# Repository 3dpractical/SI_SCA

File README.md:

# SI_SCA - Documentation

Si-SCA is a project to monitor heart rate and gyro status using Bluetooth Low Energy devices based on ESP32. This repository contain firmware for the devices to be installed.

## Library Used

 - [Adafruit MPU 6050](https://github.com/adafruit/Adafruit_MPU6050)
 - [NimBLE](https://github.com/h2zero/esp-nimble-cpp)
 - [RGB LED](https://github.com/FastLED/FastLED)
 - [FreeRTOS](https://docs.espressif.com/projects/esp-idf/en/latest/esp32/api-reference/system/freertos.html)
 - [TaskScheduler](https://github.com/arkhipenko/TaskScheduler)

## To-Do-List

- [X] ~~Establish Bluetooth Connection~~
- [X] ~~AD8232 HR Sensor Research~~
- [X] ~~Validate and Calibrate HR data~~
- [X] ~~MPU6050 get fixed Gyro data~~
- [X] ~~Validate and Calibrate Gyro data~~
- [X] ~~Get Battery Percentage Level~~
- [X] ~~Update BLE using NimBLE~~
- [X] ~~Add RGB Indicator~~
- [X] ~~Add Buzzer Indicator~~
- [X] ~~Configure Sleep Mode~~
- [X] ~~Import RTOS for better timing management~~
- [ ] Add AI for ECG signal detector

## License
This project is licensed under the MIT License - see the [LICENSE.md](LICENSE) file for details.

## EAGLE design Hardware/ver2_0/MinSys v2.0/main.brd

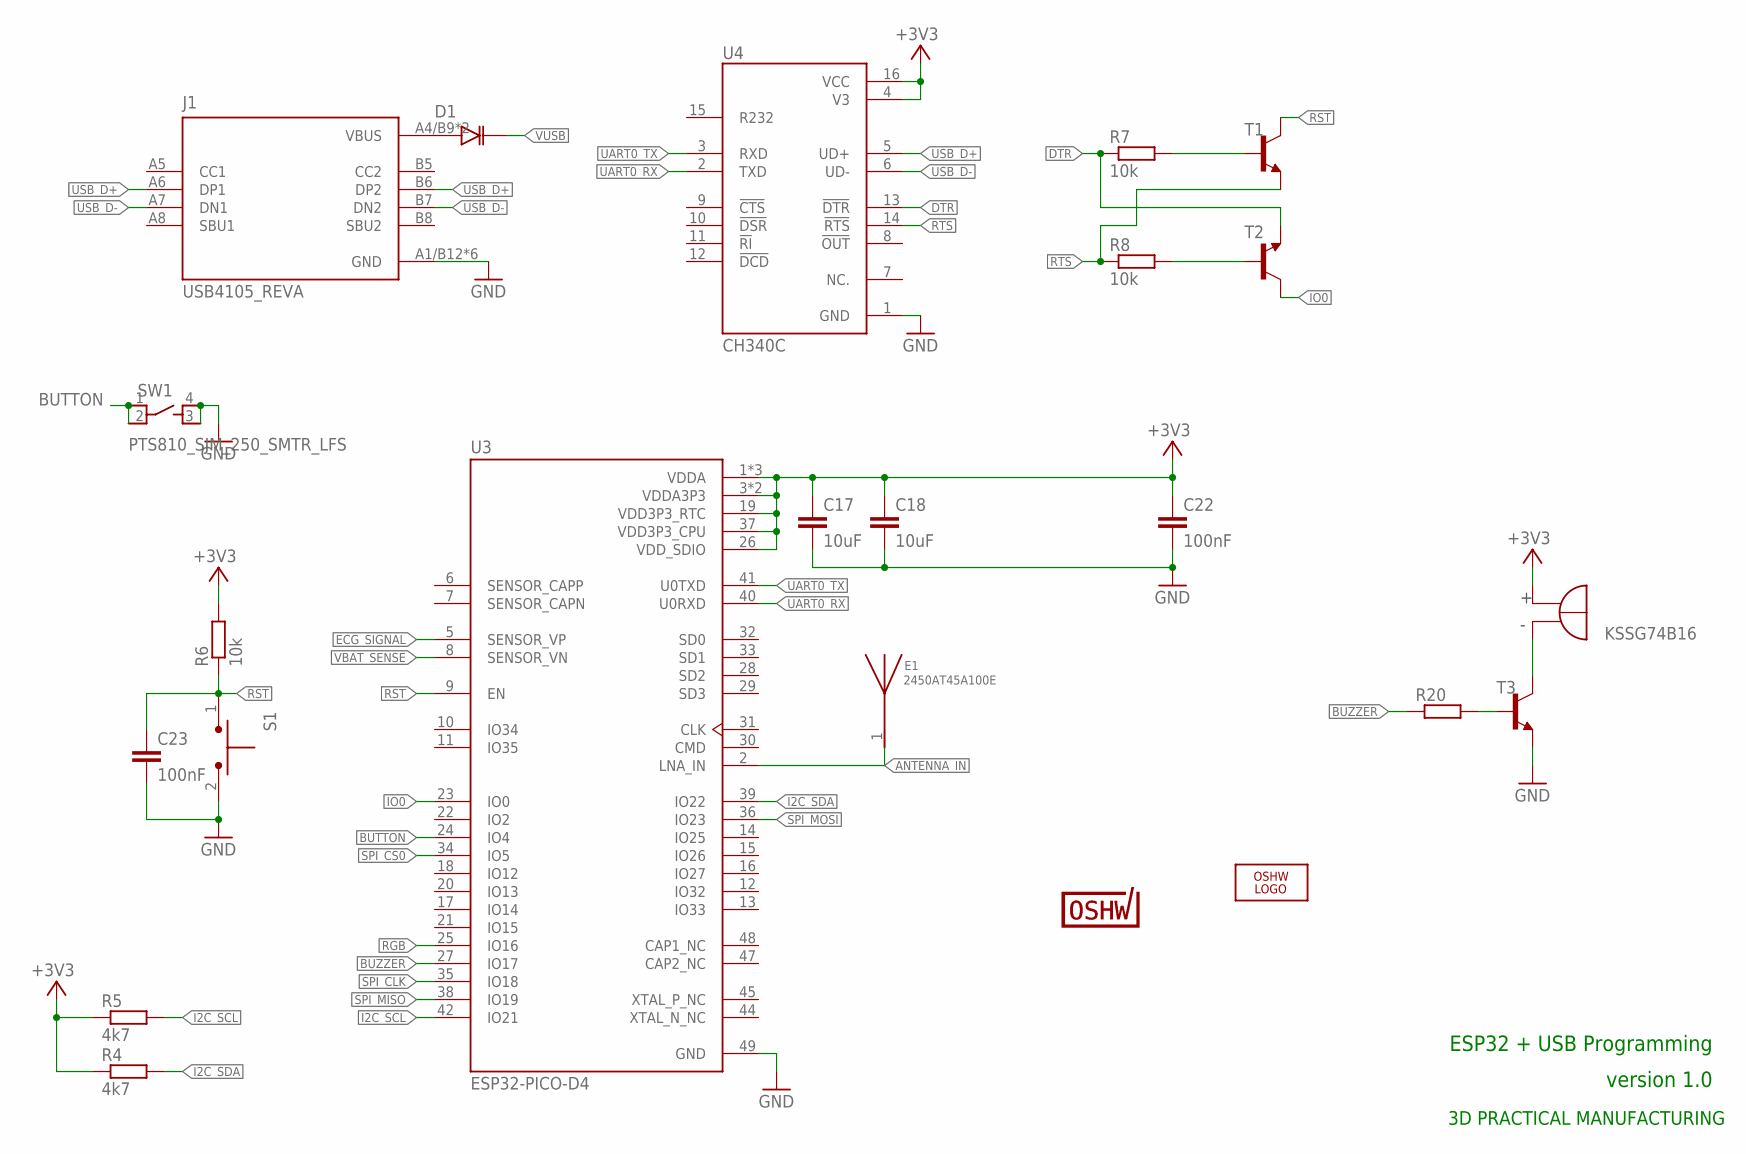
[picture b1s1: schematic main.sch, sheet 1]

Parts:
C17, C18: 10uF; C0603
C22, C23: 100nF; C0603
D1: ZMV829BTA; SOD2512X116N
E1: 2450AT45A100E; ANT_2450AT45A100E
J1: USB4105_REVA; GCT_USB4105_REVA
LOGO2: OSHW_LOGO_FILLX0200-NT; OSHW_FILLX200_NOTEXT
LS1: KSSG74B16; XDCR_KSSG74B16
R4, R5: 4k7; R0603
R6, R7, R8: 10k; R0603
R20: R-EU_R0603; R0603
S1: TL1015AF160QG; SW_TL1015AF160QG
SW1: PTS810_SJM_250_SMTR_LFS; SW_PTS810_SJM_250_SMTR_LFS
T1, T2, T3: MMBT4401LT1-NPN-SOT23-BEC; SOT23-BEC
U3: ESP32-PICO-D4; PQFN50P700X700X104-49N
U4: CH340C; SOIC127P600X180-16N
U$10: CERT-SMALL; CERT-SMALL-SILK

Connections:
+3V3: C17.1, C18.1, C22.1, LS1.P (POS), R4.1, R5.1, R6.2, U3.1 (VDDA), U3.3 (VDDA3P3), U3.4 (VDDA3P3), U3.19 (VDD3P3_RTC), U3.26 (VDD_SDIO), U3.37 (VDD3P3_CPU), U3.43 (VDDA), U3.46 (VDDA), U4.4 (V3), U4.16 (VCC); also elsewhere on the board
ANTENNA_IN: E1.1, U3.2 (LNA_IN)
BUTTON: SW1.1, SW1.2, U3.24 (IO4)
BUZZER: R20.1, U3.27 (IO17)
DTR: R7.1, T2.E, U4.13 (!DTR)
ECG_SIGNAL: U3.5 (SENSOR_VP); also elsewhere on the board
GND: C17.2, C18.2, C22.2, C23.2, J1.A1/B12 (GND), J1.B1/A12 (GND), J1.G1 (GND), J1.G2 (GND), J1.G3 (GND), J1.G4 (GND), S1.2, SW1.3, SW1.4, T3.E, U3.49 (GND), U4.1 (GND); also elsewhere on the board
I2C_SCL: R5.2, U3.42 (IO21); also elsewhere on the board
I2C_SDA: R4.2, U3.39 (IO22); also elsewhere on the board
IO0: T2.C, U3.23 (IO0)
unnamed: R7.2, T1.B
unnamed: R8.2, T2.B
unnamed: R20.2, T3.B
unnamed: D1.A, J1.A4/B9 (VBUS), J1.B4/A9 (VBUS)
unnamed: LS1.N (NEG), T3.C
RGB: U3.25 (IO16); also elsewhere on the board
RST: C23.1, R6.1, S1.1, T1.C, U3.9 (EN)
RTS: R8.1, T1.E, U4.14 (!RTS)
SPI_CLK: U3.35 (IO18)
SPI_CS0: U3.34 (IO5)
SPI_MISO: U3.38 (IO19)
SPI_MOSI: U3.36 (IO23)
UART0_RX: U3.40 (U0RXD), U4.2 (TXD)
UART0_TX: U3.41 (U0TXD), U4.3 (RXD)
USB_D+: J1.A6 (DP1), J1.B6 (DP2), U4.5 (UD+)
USB_D-: J1.A7 (DN1), J1.B7 (DN2), U4.6 (UD-)
VBAT_SENSE: U3.8 (SENSOR_VN); also elsewhere on the board
VUSB: D1.K; also elsewhere on the board

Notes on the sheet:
ESP32 + USB Programming
3D PRACTICAL MANUFACTURING
version 1.0

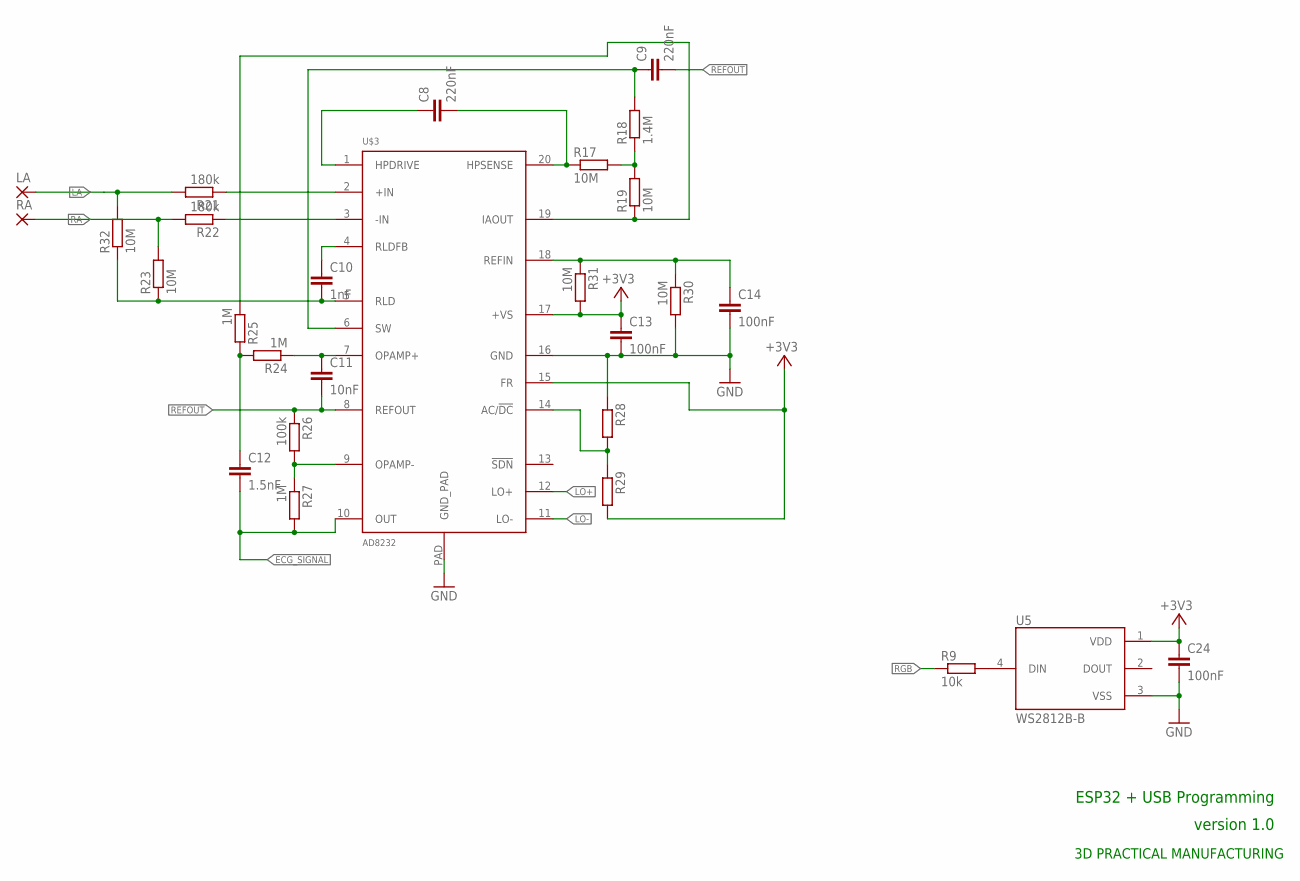
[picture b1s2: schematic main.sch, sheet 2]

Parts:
C8, C9: 220nF; C0603
C10: 1nF; C0603
C11: 10nF; C0603
C12: 1.5nF; C0603
C13, C14, C24: 100nF; C0603
LA: SMD2; SMD1,27-2,54
R9: 10k; R0603
R17, R19, R23, R30, R31, R32: 10M; R0603
R18: 1.4M; R0603
R21, R22: 180k; R0603
R24, R25, R27: 1M; R0603
R26: 100k; R0603
R28, R29: R-EU_R0603; R0603
RA: SMD2; SMD1,27-2,54
U5: WS2812B-B; LED_WS2812B-B
U$3: AD8232; LFCSP_20

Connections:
+3V3: C13.1, C24.1, R29.2, R31.2, U5.1 (VDD), U$3.15 (FR), U$3.17 (+VS); also elsewhere on the board
ECG_SIGNAL: C12.2, R27.2, U$3.10 (OUT); also elsewhere on the board
GND: C13.2, C14.2, C24.2, R28.1, R30.2, U5.3 (VSS), U$3.16 (GND), U$3.PAD (GND_PAD); also elsewhere on the board
LA: LA.1, R21.2, R32.2
LO+: U$3.12 (LO+)
LO-: U$3.11 (LO-)
unnamed: R9.2, U5.4 (DIN)
unnamed: C8.2, R17.1, U$3.20 (HPSENSE)
unnamed: C8.1, U$3.1 (HPDRIVE)
unnamed: R19.1, R25.1, U$3.19 (IAOUT)
unnamed: R17.2, R18.1, R19.2
unnamed: C9.1, R18.2, U$3.6 (SW)
unnamed: C12.1, R24.2, R25.2
unnamed: R21.1, U$3.2 (+IN)
unnamed: R22.1, U$3.3 (-IN)
unnamed: C10.1, U$3.4 (RLDFB)
unnamed: C10.2, R23.1, R32.1, U$3.5 (RLD)
unnamed: C11.1, R24.1, U$3.7 (OPAMP+)
unnamed: R26.2, R27.1, U$3.9 (OPAMP-)
unnamed: R28.2, R29.1, U$3.14 (AC/!DC)
unnamed: C14.1, R30.1, R31.1, U$3.18 (REFIN)
RA: R22.2, R23.2, RA.1
REFOUT: C9.2, C11.2, R26.1, U$3.8 (REFOUT)
RGB: R9.1; also elsewhere on the board

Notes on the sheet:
ESP32 + USB Programming
3D PRACTICAL MANUFACTURING
version 1.0

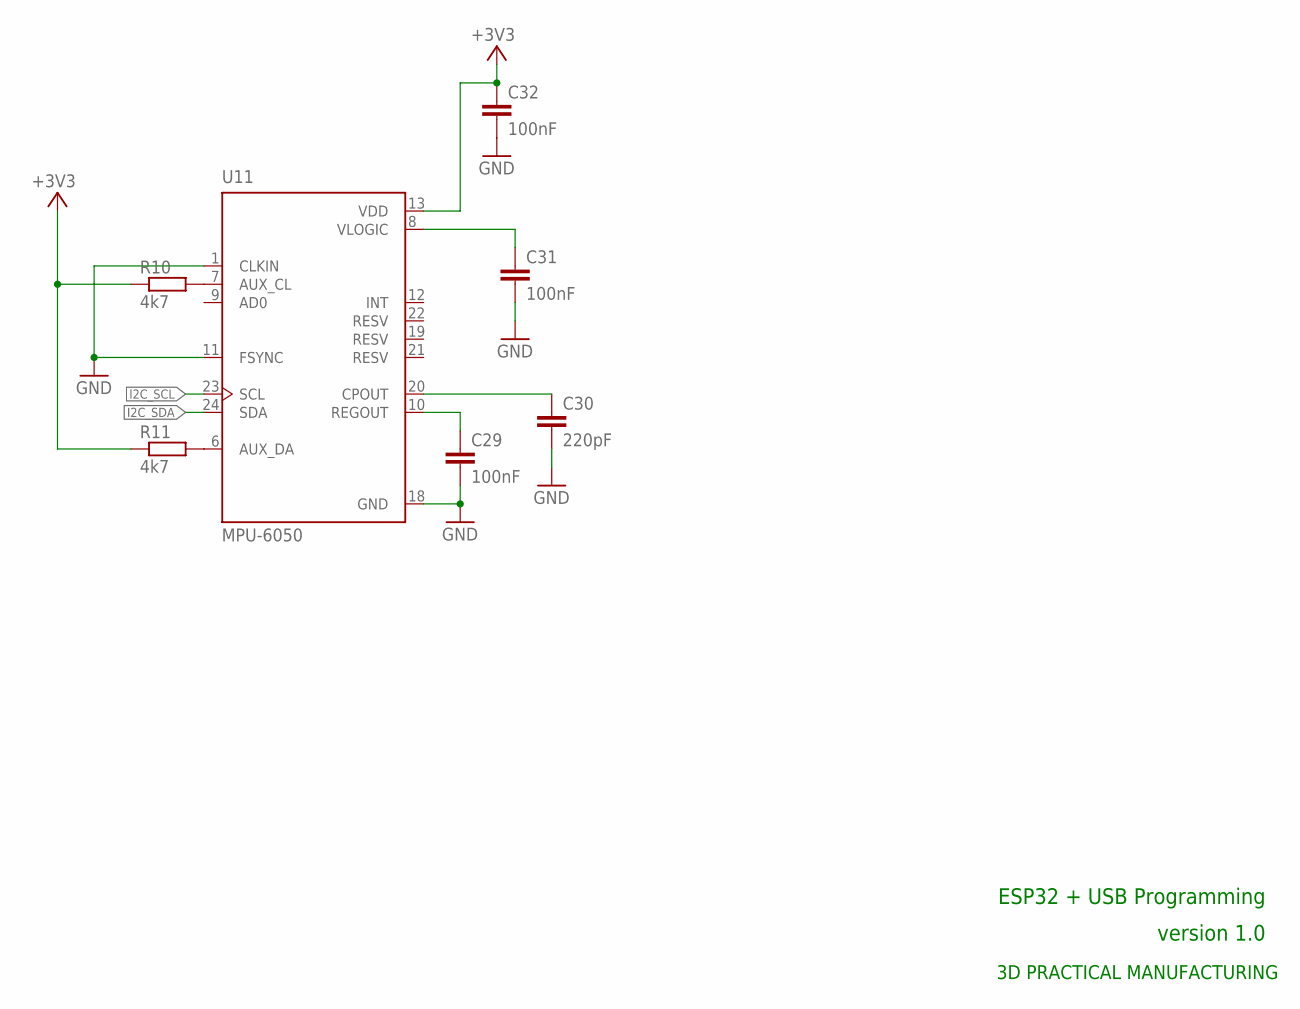
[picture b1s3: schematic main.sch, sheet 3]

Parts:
C29, C31, C32: 100nF; C0603
C30: 220pF; C0603
R10, R11: 4k7; R0603
U11: MPU-6050; QFN50P400X400X95-24N

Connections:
+3V3: C32.1, R10.1, R11.1, U11.13 (VDD); also elsewhere on the board
GND: C29.2, C30.2, C31.2, C32.2, U11.1 (CLKIN), U11.11 (FSYNC), U11.18 (GND); also elsewhere on the board
I2C_SCL: U11.23 (SCL); also elsewhere on the board
I2C_SDA: U11.24 (SDA); also elsewhere on the board
unnamed: C29.1, U11.10 (REGOUT)
unnamed: R10.2, U11.7 (AUX_CL)
unnamed: R11.2, U11.6 (AUX_DA)
unnamed: C31.1, U11.8 (VLOGIC)
unnamed: C30.1, U11.20 (CPOUT)

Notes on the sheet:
ESP32 + USB Programming
3D PRACTICAL MANUFACTURING
version 1.0

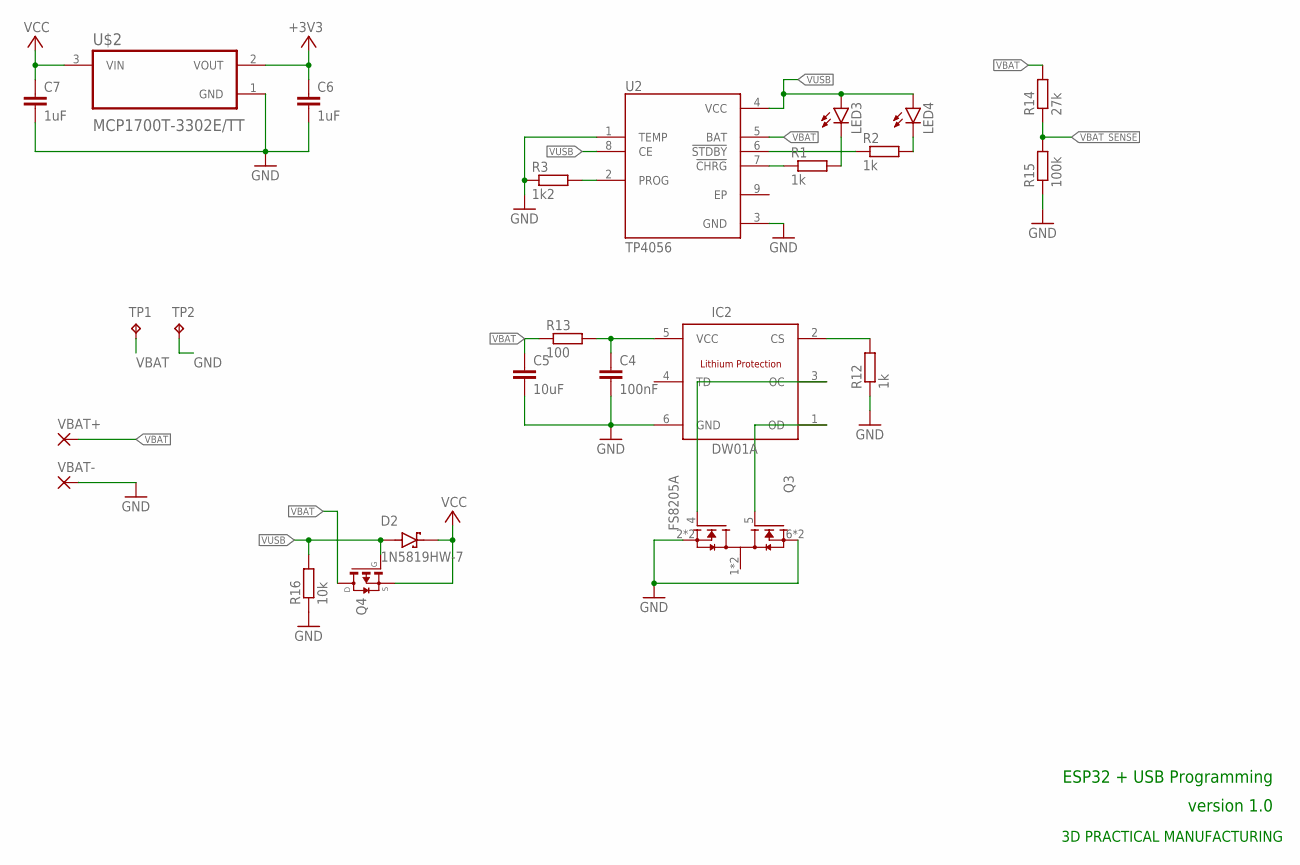
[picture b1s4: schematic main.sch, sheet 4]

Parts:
C4: 100nF; C0603
C5: 10uF; C0603
C6, C7: 1uF; C0603
D2: 1N5819HW-7; SOD3715X145N
IC2: DW01A; SOT23-6
LED3, LED4: LEDCHIP-LED0603; CHIP-LED0603
Q3: FS8205A; SOP65P640X120-8N
Q4: TRANSISTOR-FET_DMP2004K; TRANSISTOR-FET_SOT23
R1, R2, R12: 1k; R0603
R3: 1k2; R0603
R13: 100; R0603
R14: 27k; R0603
R15: 100k; R0603
R16: 10k; R0603
TP1, TP2: TPB1,27; B1,27
U2: TP4056; SOP127P600X175-9N
U$2: MCP1700T-3302E/TT; SOT95P237X112-3N
VBAT+: WIREPADSMD1,27-254; SMD1,27-2,54
VBAT-: WIREPADSMD1,27-254; SMD1,27-2,54

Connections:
+3V3: C6.1, U$2.2 (VOUT); also elsewhere on the board
GND: C4.2, C5.2, C6.2, C7.2, IC2.6 (GND), Q3.2 (S1), Q3.3 (S1), Q3.6 (S2), Q3.7 (S2), R3.1, R12.1, R15.1, R16.1, TP2.TP, U2.1 (TEMP), U2.3 (GND), U$2.1 (GND), VBAT-.1; also elsewhere on the board
unnamed: R2.1, U2.6 (!STDBY)
unnamed: LED3.C, R1.2
unnamed: LED4.C, R2.2
unnamed: R1.1, U2.7 (!CHRG)
unnamed: R3.2, U2.2 (PROG)
unnamed: IC2.1 (OD), Q3.5 (G2)
unnamed: IC2.3 (OC), Q3.4 (G1)
unnamed: IC2.2 (CS), R12.2
unnamed: C4.1, IC2.5 (VCC), R13.2
VBAT: C5.1, Q4.3 (D), R13.1, R14.2, TP1.TP, U2.5 (BAT), VBAT+.1
VBAT_SENSE: R14.1, R15.2; also elsewhere on the board
VCC: C7.1, D2.C (K), Q4.2 (S), U$2.3 (VIN)
VUSB: D2.A, LED3.A, LED4.A, Q4.1 (G), R16.2, U2.4 (VCC), U2.8 (CE); also elsewhere on the board

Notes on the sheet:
ESP32 + USB Programming
3D PRACTICAL MANUFACTURING
version 1.0

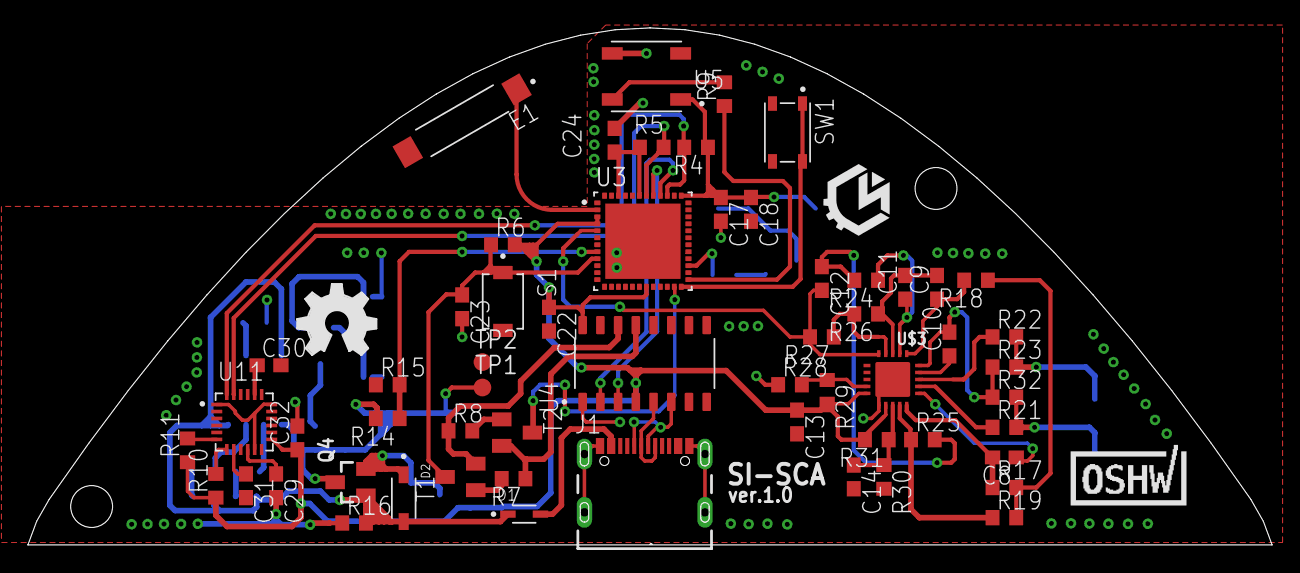
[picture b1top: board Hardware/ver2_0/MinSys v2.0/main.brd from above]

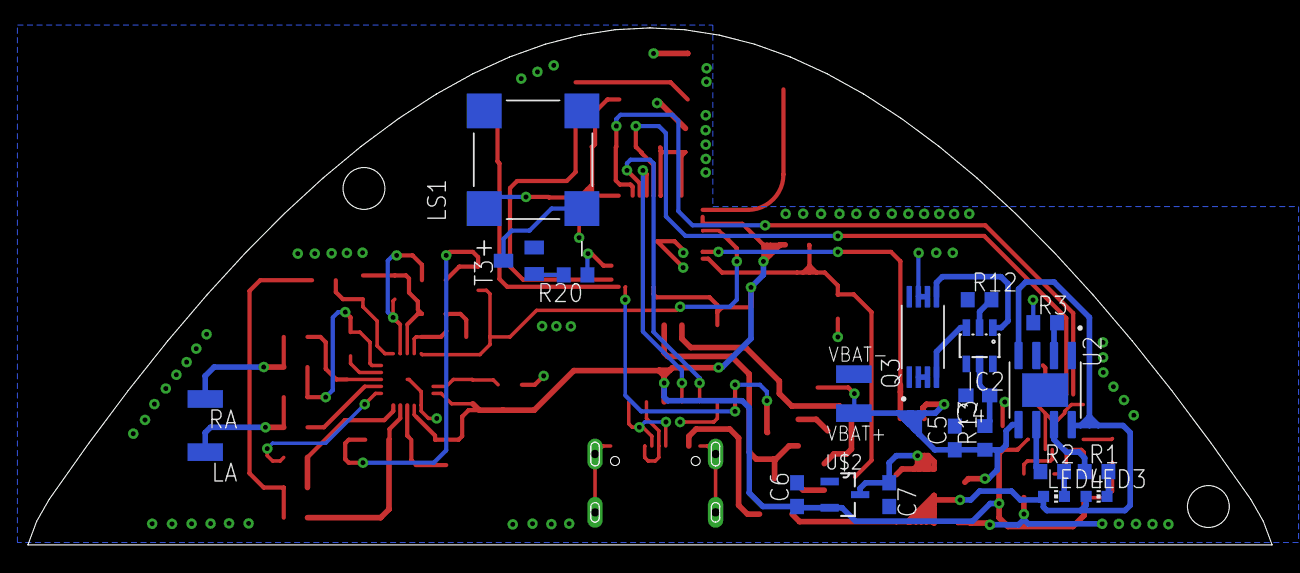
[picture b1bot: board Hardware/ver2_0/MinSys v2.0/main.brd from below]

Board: 2 copper layers, 89.2 x 37.1 mm, 82 parts (22 on the bottom side), 58 nets.

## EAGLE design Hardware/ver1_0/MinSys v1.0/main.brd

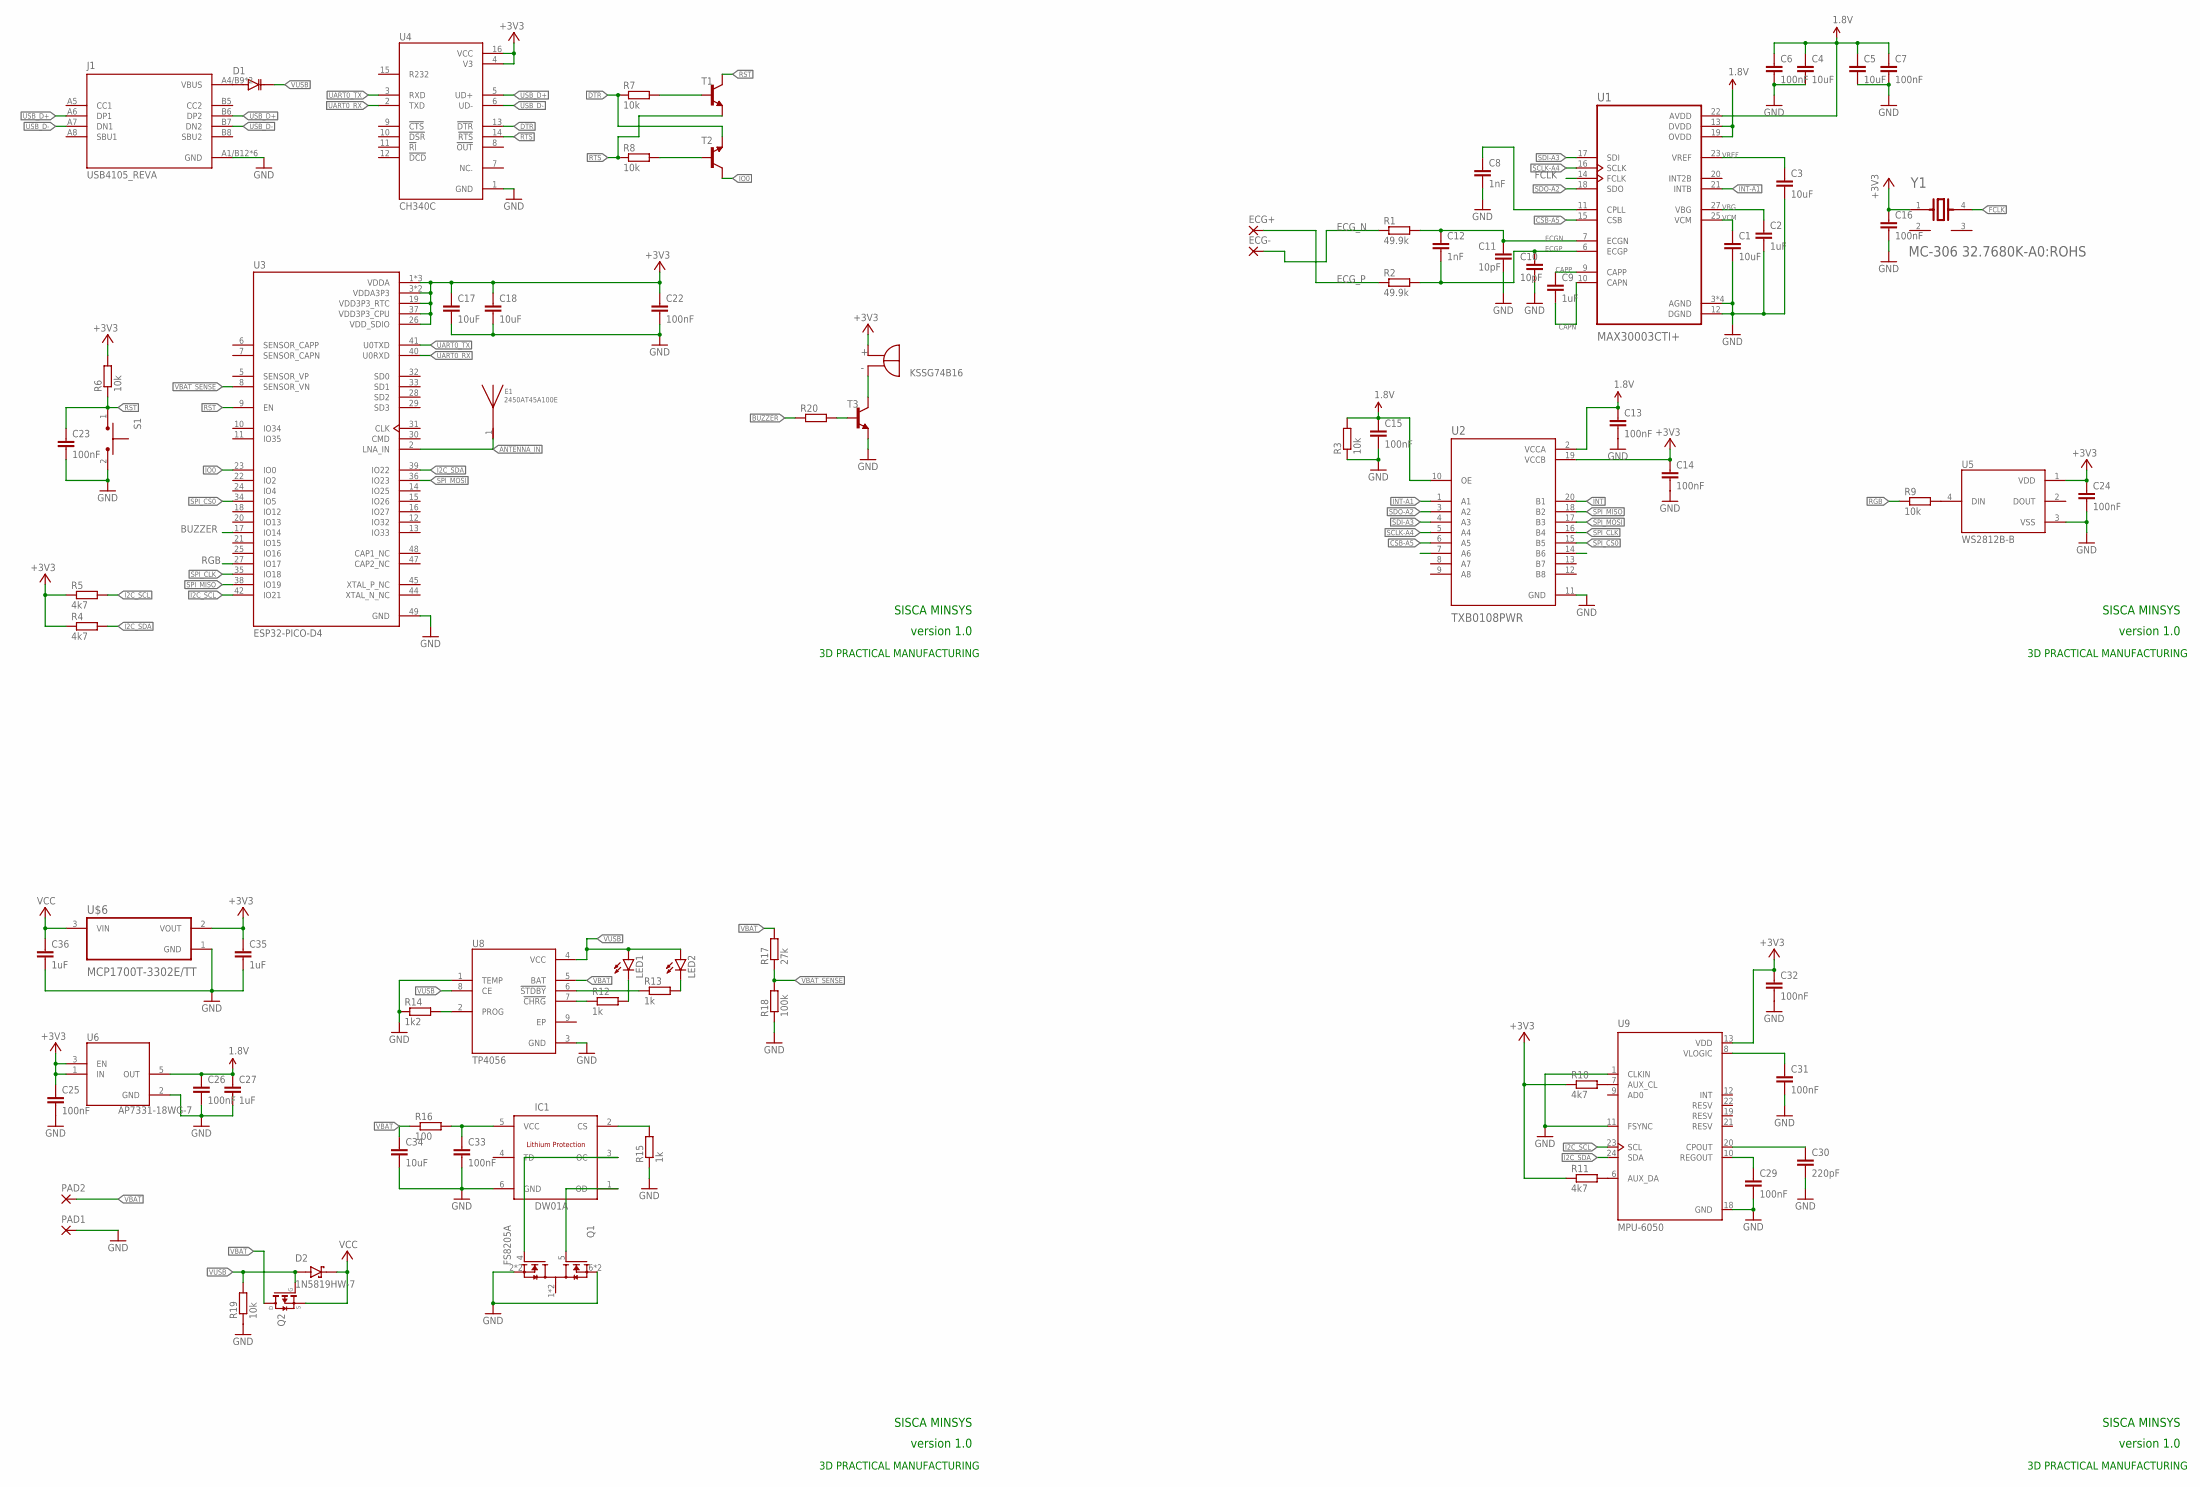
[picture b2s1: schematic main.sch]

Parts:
C1, C3, C4, C5, C17, C18, C34: 10uF; C0603
C2, C9, C27, C35, C36: 1uF; C0603
C6, C7, C13, C14, C15, C16, C22, C23, C24, C25, C26, C29, C31, C32, C33: 100nF; C0603
C8, C12: 1nF; C0603
C10, C11: 10pF; C0603
C30: 220pF; C0603
D1: ZMV829BTA; SOD2512X116N
D2: 1N5819HW-7; SOD3715X145N
E1: 2450AT45A100E; ANT_2450AT45A100E
ECG+: SMD5; SMD2,54-5,08
ECG-: SMD5; SMD2,54-5,08
IC1: DW01A; SOT23-6
J1: USB4105_REVA; GCT_USB4105_REVA
LED1, LED2: LEDCHIP-LED0603; CHIP-LED0603
LS1: KSSG74B16; XDCR_KSSG74B16
PAD1, PAD2: WIREPADSMD1,27-254; SMD1,27-2,54
Q1: FS8205A; SOP65P640X120-8N
Q2: TRANSISTOR-FET_DMP2004K; TRANSISTOR-FET_SOT23
R1, R2: 49.9k; R0603
R3, R6, R7, R8, R9, R19: 10k; R0603
R4, R5, R10, R11: 4k7; R0603
R12, R13, R15: 1k; R0603
R14: 1k2; R0603
R16: 100; R0603
R17: 27k; R0603
R18: 100k; R0603
R20: R-EU_R0603; R0603
S1: TL1015AF160QG; SW_TL1015AF160QG
T1, T2, T3: MMBT4401LT1-NPN-SOT23-BEC; SOT23-BEC
U1: MAX30003CTI+; QFN50P500X500X80-29N
U2: TXB0108PWR; SOP65P640X120-20N
U3: ESP32-PICO-D4; PQFN50P700X700X104-49N
U4: CH340C; SOIC127P600X180-16N
U5: WS2812B-B; LED_WS2812B-B
U6: AP7331-18WG-7; SOT95P285X145-5N
U8: TP4056; SOP127P600X175-9N
U9: MPU-6050; QFN50P400X400X95-24N
U$6: MCP1700T-3302E/TT; SOT95P237X112-3N
Y1: EPSON_MC-306_32.7680K-A0-ROHSEPSON_MC-306_32.7680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; EPSON_MC-306_32.7680K-A0-ROHS_0

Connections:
1.8V: C4.1, C5.1, C6.1, C7.1, C13.1, C15.1, C26.1, C27.1, R3.2, U1.13 (DVDD), U1.19 (OVDD), U1.22 (AVDD), U2.2 (VCCA), U2.10 (OE), U6.5 (OUT)
+3V3: C14.1, C16.1, C17.1, C18.1, C22.1, C24.1, C25.1, C32.1, C35.1, LS1.P (POS), R4.1, R5.1, R6.2, R10.1, R11.1, U2.19 (VCCB), U3.1 (VDDA), U3.3 (VDDA3P3), U3.4 (VDDA3P3), U3.19 (VDD3P3_RTC), U3.26 (VDD_SDIO), U3.37 (VDD3P3_CPU), U3.43 (VDDA), U3.46 (VDDA), U4.4 (V3), U4.16 (VCC), U5.1 (VDD), U6.1 (IN), U6.3 (EN), U9.13 (VDD), U$6.2 (VOUT), Y1.1
ANTENNA_IN: E1.1, U3.2 (LNA_IN)
BUZZER: R20.1, U3.17 (IO14)
CAPN: C9.2, U1.10 (CAPN)
CAPP: C9.1, U1.9 (CAPP)
CSB-A5: U1.15 (CSB), U2.6 (A5)
DTR: R7.1, T2.E, U4.13 (!DTR)
ECGN: C11.1, C12.1, R1.2, U1.7 (ECGN)
ECGP: C10.1, C12.2, R2.2, U1.6 (ECGP)
ECG_N: ECG-.1, R1.1
ECG_P: ECG+.1, R2.1
FCLK: U1.14 (FCLK), Y1.4
GND: C1.2, C2.2, C3.2, C4.2, C5.2, C6.2, C7.2, C8.2, C10.2, C11.2, C13.2, C14.2, C15.2, C16.2, C17.2, C18.2, C22.2, C23.2, C24.2, C25.2, C26.2, C27.2, C29.2, C30.2, C31.2, C32.2, C33.2, C34.2, C35.2, C36.2, IC1.6 (GND), J1.A1/B12 (GND), J1.B1/A12 (GND), J1.G1 (GND), J1.G2 (GND), J1.G3 (GND), J1.G4 (GND), PAD1.1, Q1.2 (S1), Q1.3 (S1), Q1.6 (S2), Q1.7 (S2), R3.1, R14.1, R15.1, R18.1, R19.1, S1.2, T3.E, U1.3 (AGND), U1.8 (AGND), U1.12 (DGND), U1.28 (AGND), U1.29 (AGND), U2.11 (GND), U3.49 (GND), U4.1 (GND), U5.3 (VSS), U6.2 (GND), U8.1 (TEMP), U8.3 (GND), U9.1 (CLKIN), U9.11 (FSYNC), U9.18 (GND), U$6.1 (GND)
I2C_SCL: R5.2, U3.42 (IO21), U9.23 (SCL)
I2C_SDA: R4.2, U3.39 (IO22), U9.24 (SDA)
INT: U2.20 (B1)
INT-A1: U1.21 (INTB), U2.1 (A1)
IO0: T2.C, U3.23 (IO0)
unnamed: R7.2, T1.B
unnamed: R8.2, T2.B
unnamed: R9.2, U5.4 (DIN)
unnamed: C8.1, U1.11 (CPLL)
unnamed: R20.2, T3.B
unnamed: R10.2, U9.7 (AUX_CL)
unnamed: R11.2, U9.6 (AUX_DA)
unnamed: C29.1, U9.10 (REGOUT)
unnamed: C30.1, U9.20 (CPOUT)
unnamed: R13.1, U8.6 (!STDBY)
unnamed: LED1.C, R12.2
unnamed: LED2.C, R13.2
unnamed: R12.1, U8.7 (!CHRG)
unnamed: R14.2, U8.2 (PROG)
unnamed: IC1.1 (OD), Q1.5 (G2)
unnamed: IC1.3 (OC), Q1.4 (G1)
unnamed: IC1.2 (CS), R15.2
unnamed: C33.1, IC1.5 (VCC), R16.2
unnamed: D1.A, J1.A4/B9 (VBUS), J1.B4/A9 (VBUS)
unnamed: C31.1, U9.8 (VLOGIC)
unnamed: LS1.N (NEG), T3.C
RGB: R9.1, U3.27 (IO17)
RST: C23.1, R6.1, S1.1, T1.C, U3.9 (EN)
RTS: R8.1, T1.E, U4.14 (!RTS)
SCLK-A4: U1.16 (SCLK), U2.5 (A4)
SDI-A3: U1.17 (SDI), U2.4 (A3)
SDO-A2: U1.18 (SDO), U2.3 (A2)
SPI_CLK: U2.16 (B4), U3.35 (IO18)
SPI_CS0: U2.15 (B5), U3.34 (IO5)
SPI_MISO: U2.18 (B2), U3.38 (IO19)
SPI_MOSI: U2.17 (B3), U3.36 (IO23)
UART0_RX: U3.40 (U0RXD), U4.2 (TXD)
UART0_TX: U3.41 (U0TXD), U4.3 (RXD)
USB_D+: J1.A6 (DP1), J1.B6 (DP2), U4.5 (UD+)
USB_D-: J1.A7 (DN1), J1.B7 (DN2), U4.6 (UD-)
VBAT: C34.1, PAD2.1, Q2.3 (D), R16.1, R17.2, U8.5 (BAT)
VBAT_SENSE: R17.1, R18.2, U3.8 (SENSOR_VN)
VBG: C2.1, U1.27 (VBG)
VCC: C36.1, D2.C (K), Q2.2 (S), U$6.3 (VIN)
VCM: C1.1, U1.25 (VCM)
VREF: C3.1, U1.23 (VREF)
VUSB: D1.K, D2.A, LED1.A, LED2.A, Q2.1 (G), R19.2, U8.4 (VCC), U8.8 (CE)

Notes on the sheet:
SISCA MINSYS
3D PRACTICAL MANUFACTURING
version 1.0

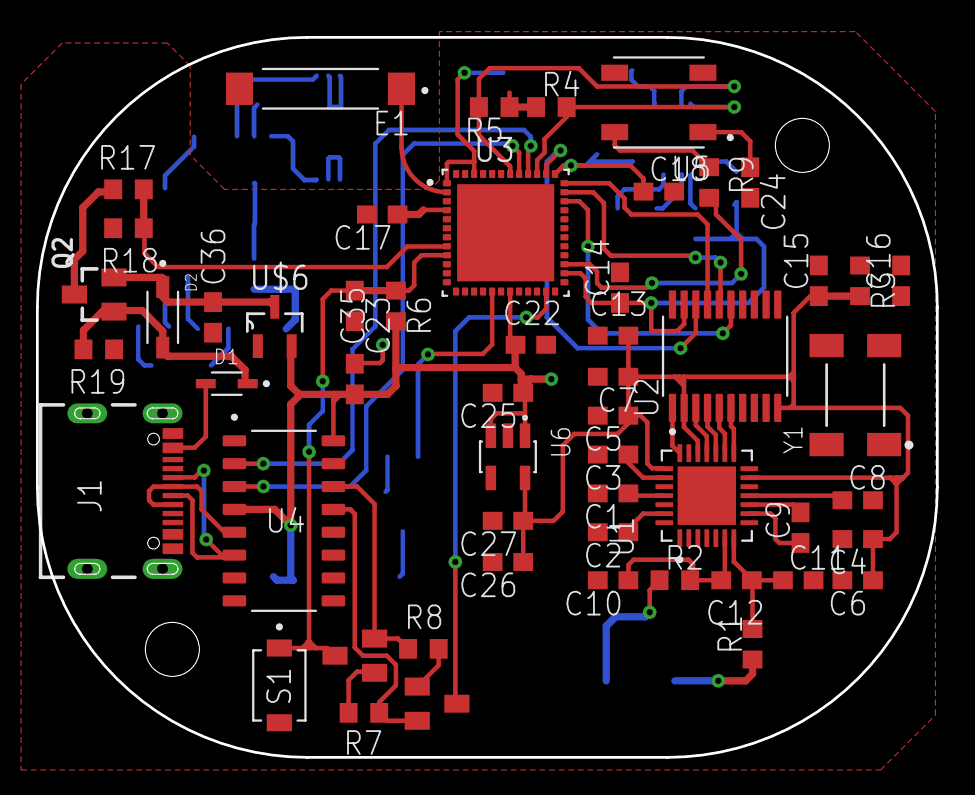
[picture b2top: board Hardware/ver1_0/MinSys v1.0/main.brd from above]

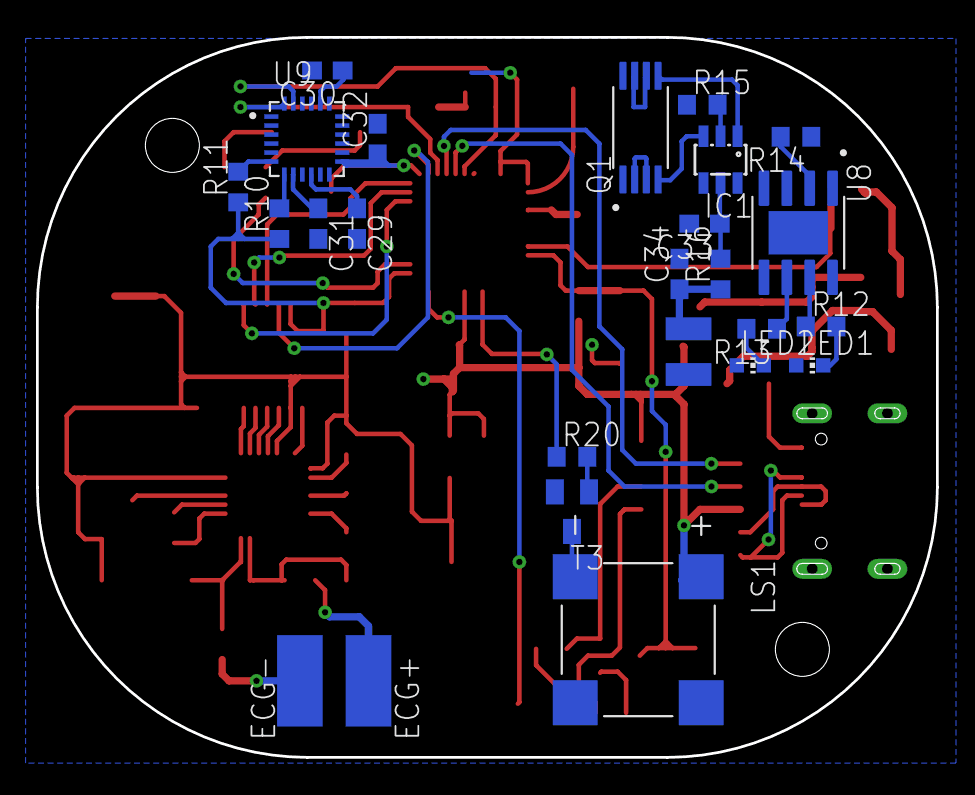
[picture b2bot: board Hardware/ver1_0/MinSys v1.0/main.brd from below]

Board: 2 copper layers, 50.0 x 40.0 mm, 80 parts (26 on the bottom side), 60 nets.

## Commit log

2022-12-08 Upload files
2022-12-08 add software submodules
2022-12-08 Add submodules
2022-12-08 Change folder
2022-12-08 change cubmodules
2022-12-08 Add app submodules
